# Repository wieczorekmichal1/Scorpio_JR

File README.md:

# Scorpio_JR
Circut design and software for Scorpio Junior rover

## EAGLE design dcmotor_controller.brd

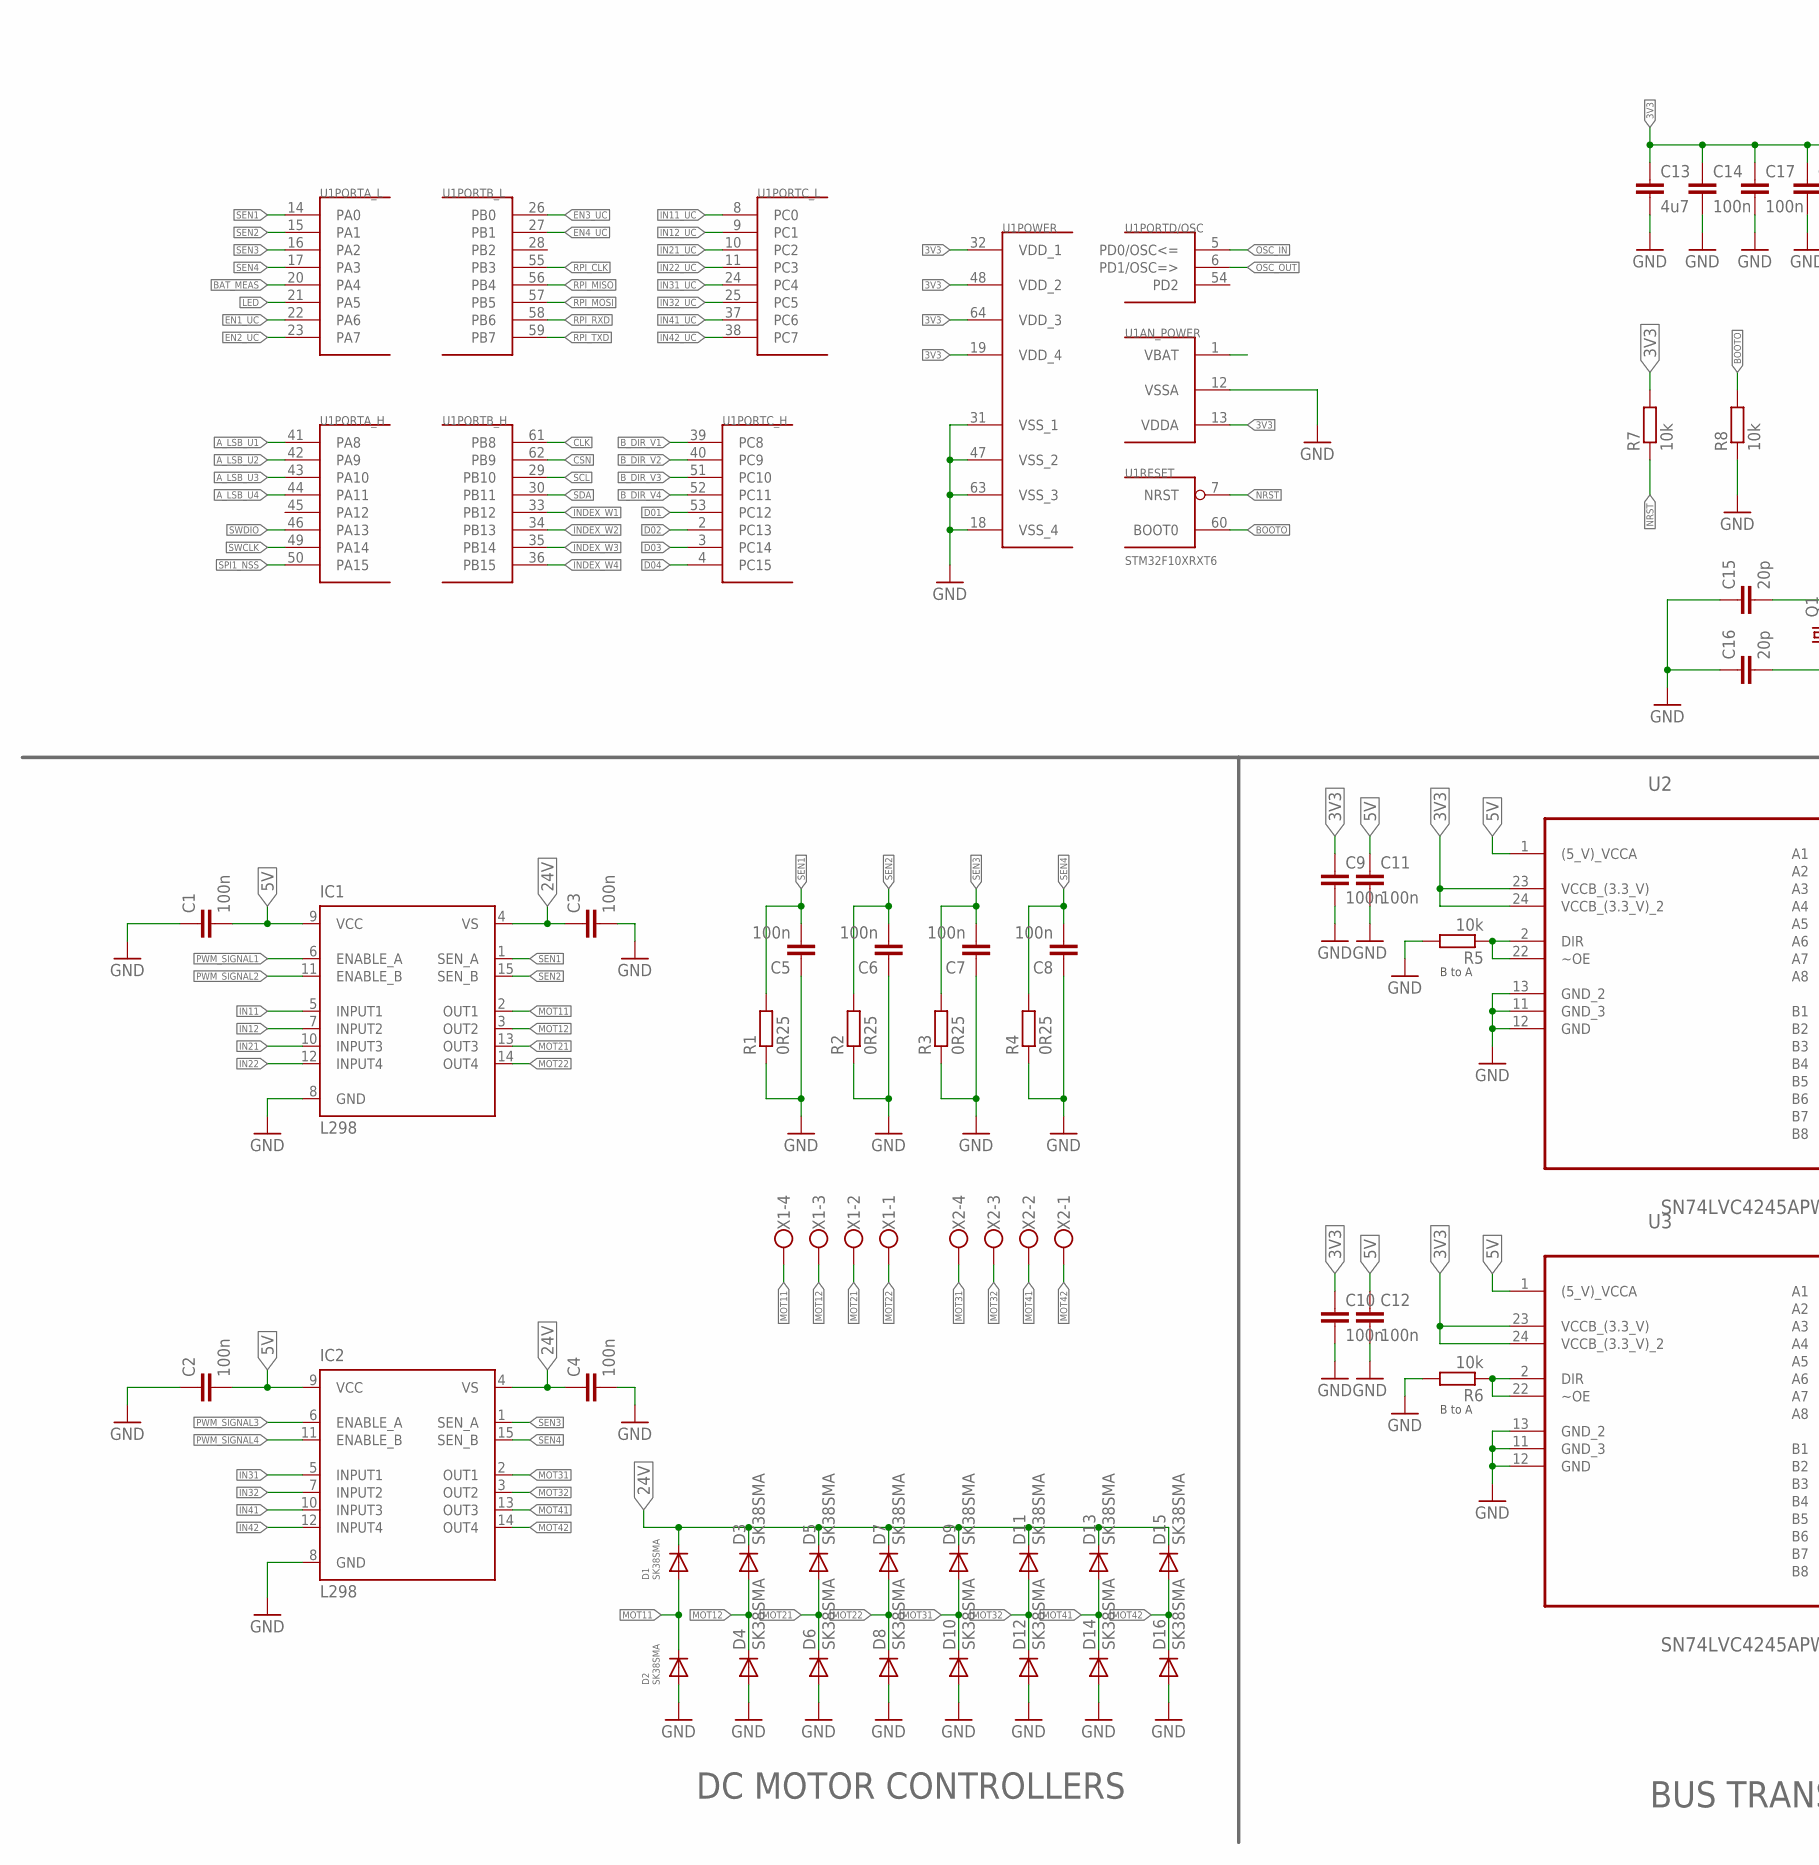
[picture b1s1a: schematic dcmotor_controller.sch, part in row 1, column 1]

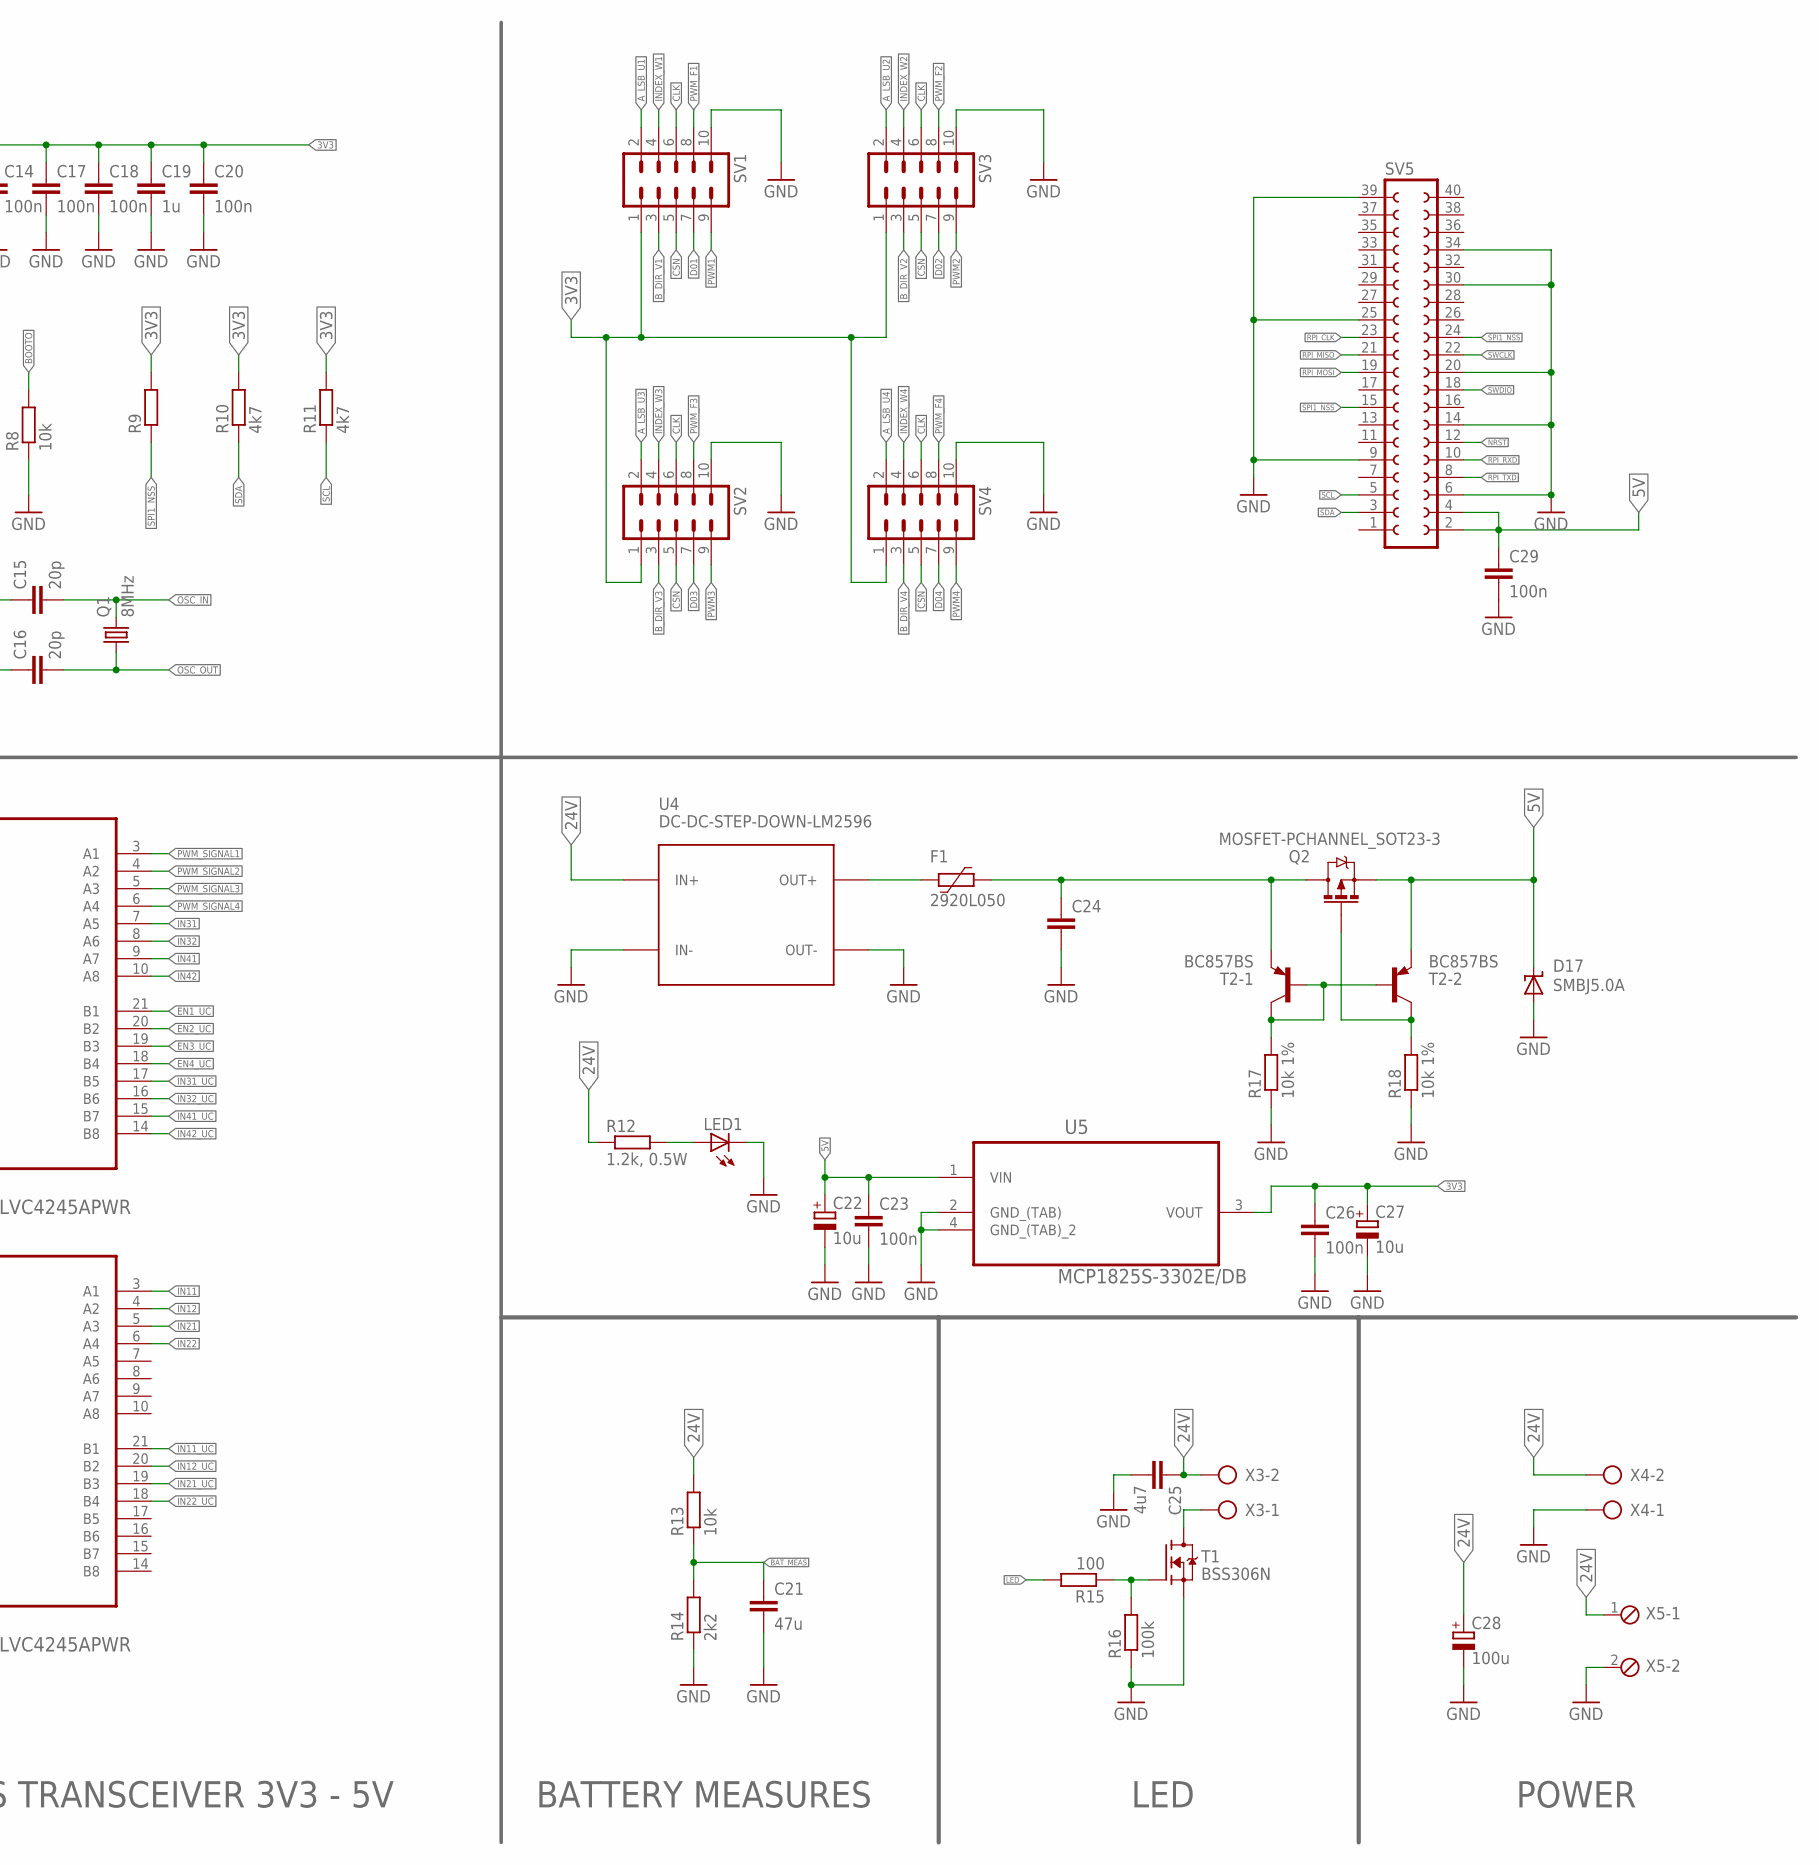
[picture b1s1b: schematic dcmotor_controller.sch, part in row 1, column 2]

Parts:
C1, C2, C3, C4, C5, C6, C7, C8, C9, C10, C11, C12, C14, C17, C18, C20, C23, C26, C29: 100n; C0805
C13, C25: 4u7; C0805
C15, C16: 20p; C0805
C19: 1u; C0805
C21: 47u; C0805
C22, C27: 10u; 153CLV-0807
C24: C-EUC0805; C0805
C28: 100u; 153CLV-0807
D1, D2, D3, D4, D5, D6, D7, D8, D9, D10, D11, D12, D13, D14, D15, D16: SK38SMA; DO214AC
D17: SMBJ5.0A; SMBJ
F1: 2920L050; 2920L
IC1, IC2: L298; MULTIWATT-15
LED1: LEDCHIPLED_0805; CHIPLED_0805
Q1: 8MHz; CSM-7X-DU
Q2: MOSFET-PCHANNEL_SOT23-3; SOT23-3
R1, R2, R3, R4: 0R25; R2512
R5, R6, R13: 10k; M0805
R7, R8: 10k; R0805
R9: R-EU_R0805; R0805
R10, R11: 4k7; R0805
R12: 1.2k, 0.5W; R2010
R14: 2k2; M0805
R15: 100; M0805
R16: 100k; M0805
R17, R18: 10k 1%; M0805
SV1, SV2, SV3, SV4: ML10L
SV5: FE20-2
T1: BSS306N; SOT23
T2: BC857BS; SOT363
U1: STM32F10XRXT6; TQFP64
U2, U3: SN74LVC4245APWR; SOP65P640X120-24N
U4: DC-DC-STEP-DOWN-LM2596
U5: MCP1825S-3302E/DB; SOT230P700X180-4N
X1, X2: W237-4
X3, X4: AK500/2
X5: MPT2; 2POL254

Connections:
3V3: C9.1, C10.1, C13.1, C14.1, C17.1, C18.1, C19.1, C20.1, C26.1, C27.+, R7.2, R9.2, R10.2, R11.2, SV1.1, SV2.1, SV3.1, SV4.1, U1.13 (VDDA), U1.19 (VDD_4), U1.32 (VDD_1), U1.48 (VDD_2), U1.64 (VDD_3), U2.23 (VCCB_(3.3_V)), U2.24 (VCCB_(3.3_V)_2), U3.23 (VCCB_(3.3_V)), U3.24 (VCCB_(3.3_V)_2), U5.3 (VOUT)
5V: C1.2, C2.2, C11.1, C12.1, C22.+, C23.1, C29.1, D17.C, IC1.9 (VCC), IC2.9 (VCC), Q2.2 (S), SV5.2, SV5.4, T2.4 (E), U2.1 ((5_V)_VCCA), U3.1 ((5_V)_VCCA), U5.1 (VIN)
24V: C3.1, C4.1, C25.1, C28.+, D1.C, D3.C, D5.C, D7.C, D9.C, D11.C, D13.C, D15.C, IC1.4 (VS), IC2.4 (VS), R12.1, R13.2, U4.IN+, X3.2, X4.2, X5.1
A_LSB_U1: SV1.2, U1.41 (PA8)
A_LSB_U2: SV3.2, U1.42 (PA9)
A_LSB_U3: SV2.2, U1.43 (PA10)
A_LSB_U4: SV4.2, U1.44 (PA11)
BAT_MEAS: C21.1, R13.1, R14.2, U1.20 (PA4)
BOOTO: R8.2, U1.60 (BOOT0)
B_DIR_V1: SV1.3, U1.39 (PC8)
B_DIR_V2: SV3.3, U1.40 (PC9)
B_DIR_V3: SV2.3, U1.51 (PC10)
B_DIR_V4: SV4.3, U1.52 (PC11)
CLK: SV1.6, SV2.6, SV3.6, SV4.6, U1.61 (PB8)
CSN: SV1.5, SV2.5, SV3.5, SV4.5, U1.62 (PB9)
D01: SV1.7, U1.53 (PC12)
D02: SV3.7, U1.2 (PC13)
D03: SV2.7, U1.3 (PC14)
D04: SV4.7, U1.4 (PC15)
EN1_UC: U1.22 (PA6), U2.21 (B1)
EN2_UC: U1.23 (PA7), U2.20 (B2)
EN3_UC: U1.26 (PB0), U2.19 (B3)
EN4_UC: U1.27 (PB1), U2.18 (B4)
GND: C1.1, C2.1, C3.2, C4.2, C5.1, C6.1, C7.1, C8.1, C9.2, C10.2, C11.2, C12.2, C13.2, C14.2, C15.1, C16.1, C17.2, C18.2, C19.2, C20.2, C21.2, C22.-, C23.2, C24.2, C25.2, C26.2, C27.-, C28.-, C29.2, D2.A, D4.A, D6.A, D8.A, D10.A, D12.A, D14.A, D16.A, D17.A, IC1.8 (GND), IC2.8 (GND), LED1.C, R1.1, R2.1, R3.1, R4.1, R5.2, R6.2, R8.1, R14.1, R16.1, R17.1, R18.1, SV1.10, SV2.10, SV3.10, SV4.10, SV5.6, SV5.9, SV5.14, SV5.20, SV5.25, SV5.30, SV5.34, SV5.39, T1.2 (S), U1.12 (VSSA), U1.18 (VSS_4), U1.31 (VSS_1), U1.47 (VSS_2), U1.63 (VSS_3), U2.11 (GND_3), U2.12 (GND), U2.13 (GND_2), U3.11 (GND_3), U3.12 (GND), U3.13 (GND_2), U4.IN-, U4.OUT-, U5.2 (GND_(TAB)), U5.4 (GND_(TAB)_2), X4.1, X5.2
IN11: IC1.5 (INPUT1), U3.3 (A1)
IN11_UC: U1.8 (PC0), U3.21 (B1)
IN12: IC1.7 (INPUT2), U3.4 (A2)
IN12_UC: U1.9 (PC1), U3.20 (B2)
IN21: IC1.10 (INPUT3), U3.5 (A3)
IN21_UC: U1.10 (PC2), U3.19 (B3)
IN22: IC1.12 (INPUT4), U3.6 (A4)
IN22_UC: U1.11 (PC3), U3.18 (B4)
IN31: IC2.5 (INPUT1), U2.7 (A5)
IN31_UC: U1.24 (PC4), U2.17 (B5)
IN32: IC2.7 (INPUT2), U2.8 (A6)
IN32_UC: U1.25 (PC5), U2.16 (B6)
IN41: IC2.10 (INPUT3), U2.9 (A7)
IN41_UC: U1.37 (PC6), U2.15 (B7)
IN42: IC2.12 (INPUT4), U2.10 (A8)
IN42_UC: U1.38 (PC7), U2.14 (B8)
INDEX_W1: SV1.4, U1.33 (PB12)
INDEX_W2: SV3.4, U1.34 (PB13)
INDEX_W3: SV2.4, U1.35 (PB14)
INDEX_W4: SV4.4, U1.36 (PB15)
LED: R15.2, U1.21 (PA5)
MOT11: D1.A, D2.C, IC1.2 (OUT1), X1.4
MOT12: D3.A, D4.C, IC1.3 (OUT2), X1.3
MOT21: D5.A, D6.C, IC1.13 (OUT3), X1.2
MOT22: D7.A, D8.C, IC1.14 (OUT4), X1.1
MOT31: D9.A, D10.C, IC2.2 (OUT1), X2.4
MOT32: D11.A, D12.C, IC2.3 (OUT2), X2.3
MOT41: D13.A, D14.C, IC2.13 (OUT3), X2.2
MOT42: D15.A, D16.C, IC2.14 (OUT4), X2.1
unnamed: F1.2, U4.OUT+
unnamed: LED1.A, R12.2
unnamed: R5.1, U2.2 (DIR), U2.22 (~OE)
unnamed: R6.1, U3.2 (DIR), U3.22 (~OE)
unnamed: C24.1, F1.1, Q2.3 (D), T2.1 (E)
unnamed: Q2.1 (G), R18.2, T2.3 (C)
unnamed: R17.2, T2.2 (B), T2.5 (B), T2.6 (C)
unnamed: R15.1, R16.2, T1.1 (G)
unnamed: T1.3 (D), X3.1
NRST: R7.1, SV5.12, U1.7 (NRST)
OSC_IN: C15.2, Q1.2, U1.5 (PD0/OSC<=)
OSC_OUT: C16.2, Q1.1, U1.6 (PD1/OSC=>)
PWM1: SV1.9
PWM2: SV3.9
PWM3: SV2.9
PWM4: SV4.9
PWM_F1: SV1.8
PWM_F2: SV3.8
PWM_F3: SV2.8
PWM_F4: SV4.8
PWM_SIGNAL1: IC1.6 (ENABLE_A), U2.3 (A1)
PWM_SIGNAL2: IC1.11 (ENABLE_B), U2.4 (A2)
PWM_SIGNAL3: IC2.6 (ENABLE_A), U2.5 (A3)
PWM_SIGNAL4: IC2.11 (ENABLE_B), U2.6 (A4)
RPI_CLK: SV5.23, U1.55 (PB3)
RPI_MISO: SV5.21, U1.56 (PB4)
RPI_MOSI: SV5.19, U1.57 (PB5)
RPI_RXD: SV5.10, U1.58 (PB6)
RPI_TXD: SV5.8, U1.59 (PB7)
SCL: R11.1, SV5.5, U1.29 (PB10)
SDA: R10.1, SV5.3, U1.30 (PB11)
SEN1: C5.2, IC1.1 (SEN_A), R1.2, U1.14 (PA0)
SEN2: C6.2, IC1.15 (SEN_B), R2.2, U1.15 (PA1)
SEN3: C7.2, IC2.1 (SEN_A), R3.2, U1.16 (PA2)
SEN4: C8.2, IC2.15 (SEN_B), R4.2, U1.17 (PA3)
SPI1_NSS: R9.1, SV5.15, SV5.24, U1.50 (PA15)
SWCLK: SV5.22, U1.49 (PA14)
SWDIO: SV5.18, U1.46 (PA13)

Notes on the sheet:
DC MOTOR CONTROLLERS
BUS TRANSCEIVER 3V3 - 5V
BATTERY MEASURES
LED
POWER
B to A

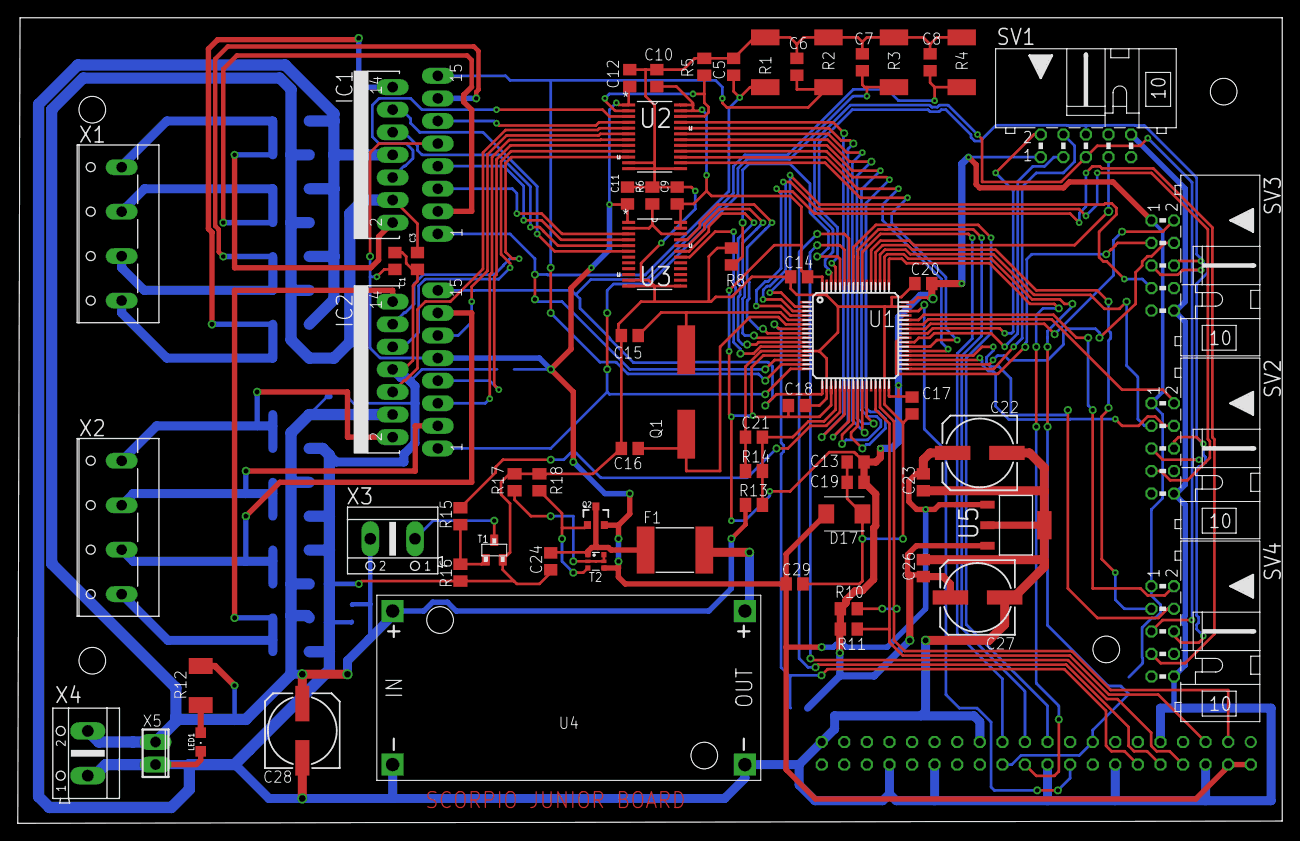
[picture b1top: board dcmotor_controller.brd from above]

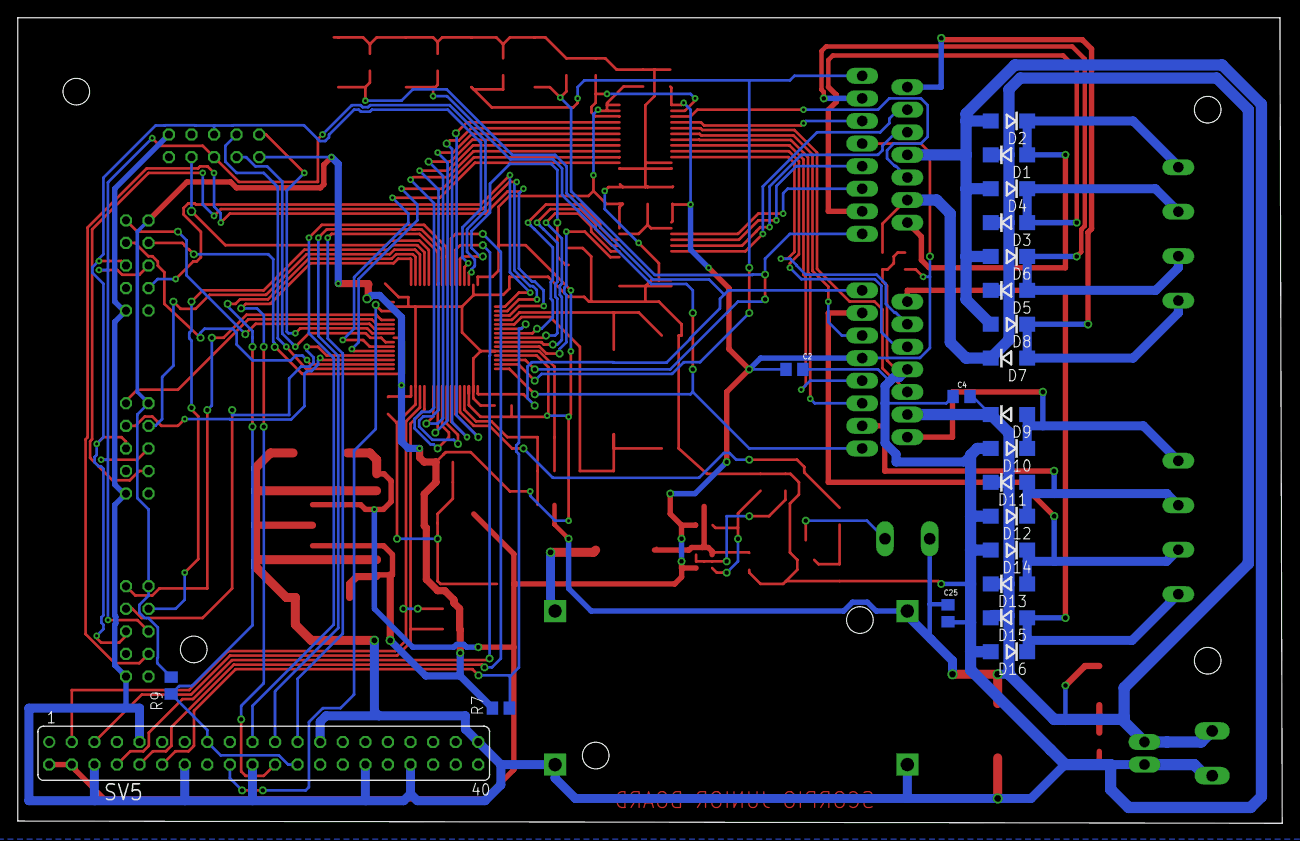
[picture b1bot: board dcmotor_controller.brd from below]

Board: 2 copper layers, 142.2 x 90.6 mm, 87 parts (22 on the bottom side), 83 nets.

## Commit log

2018-04-03 dodana przetwornica
2018-04-04 poprawione zasilanie
2018-04-06 dupaaa
2018-04-06 nie wszystkie elementy rozmieszczone
2018-04-08 update - clean - parts
2018-04-08 3dmodel added
2018-04-11 airwires connected, names
2018-04-11 poprawione umiejscowienie kondensatorów
2018-04-11 mini poprawka
2018-04-26 poprawione przelotki
2018-04-26 plus mała poprawka
2018-05-04 dodana masa
2018-05-12 some drc rules, airwires repaired and schemat checked
2018-05-13 rpi header repaired
2018-05-13 renumber parts, small changes in layout

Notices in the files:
parts and their libraries:
NXP_60_26022015: This library may be distributed and adapted freely for any purpose, as long as NXP is credited and any new creation is licensed under the same terms.
lm2596: Released under the Creative Commons Attribution 4.0 International License: http://creativecommons.org/licenses/by/4.0
